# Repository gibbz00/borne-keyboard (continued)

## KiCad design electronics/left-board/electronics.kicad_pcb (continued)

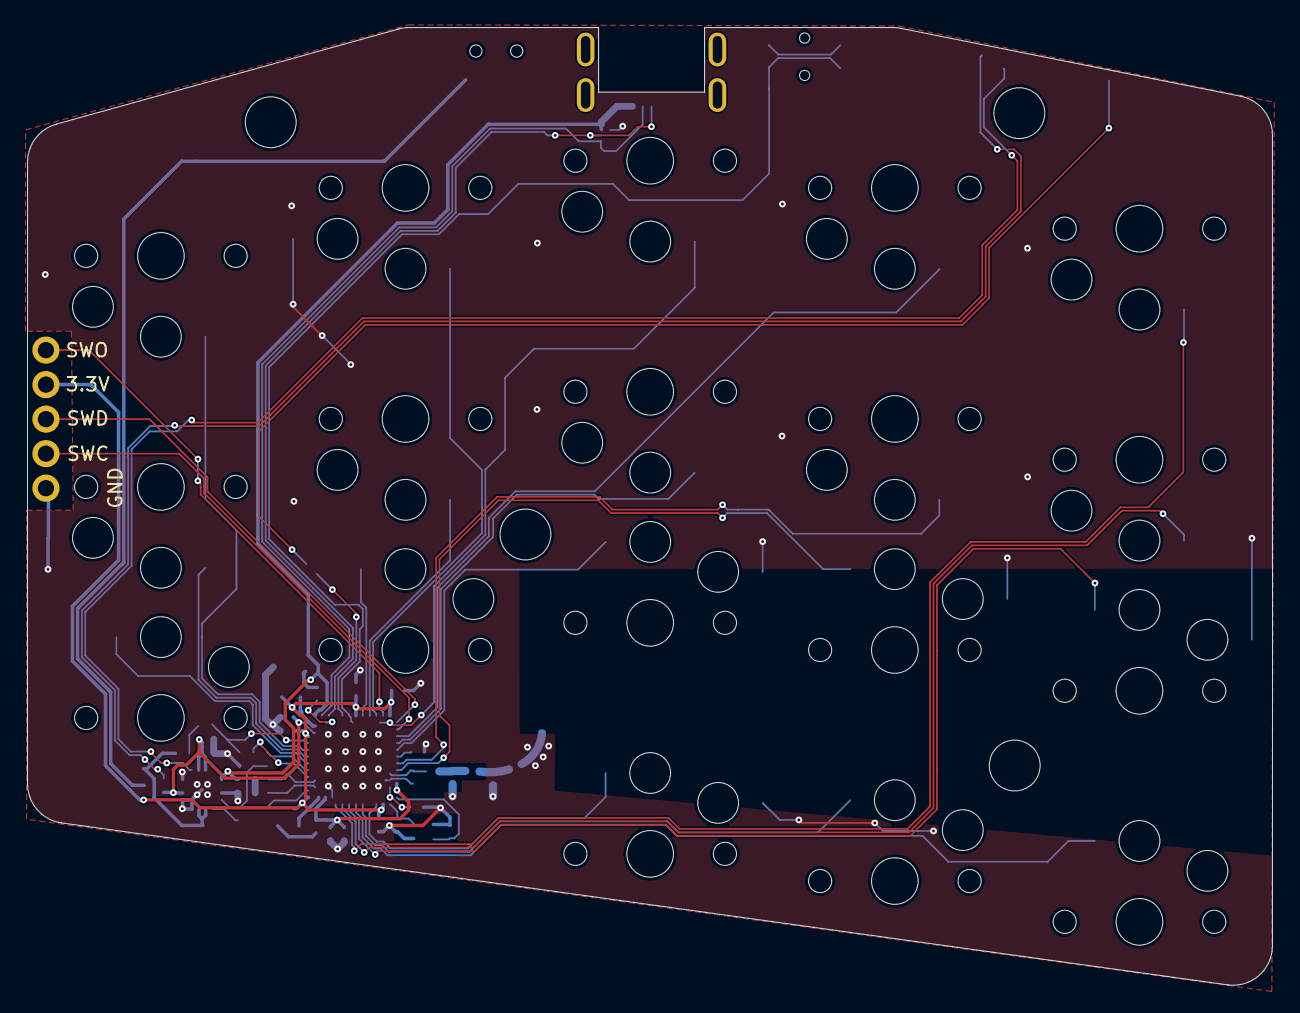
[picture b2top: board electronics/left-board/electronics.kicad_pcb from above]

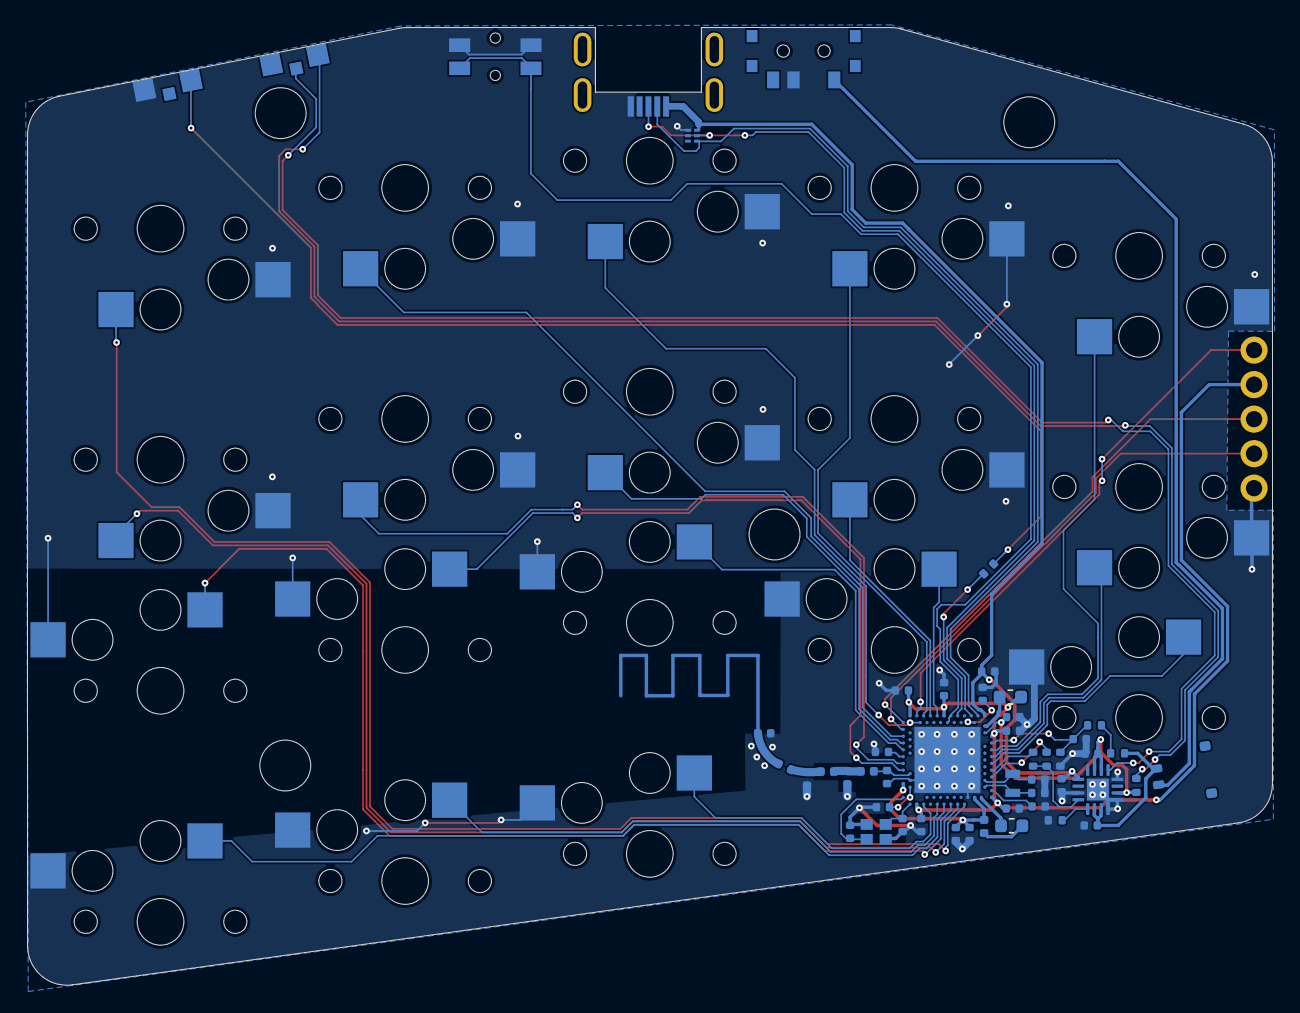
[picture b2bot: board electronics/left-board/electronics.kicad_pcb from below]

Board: 2 copper layers, 91.6 x 70.5 mm, 79 parts (74 on the bottom side), 57 nets.

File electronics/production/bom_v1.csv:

Qty,Reference(s),Value,Footprint,JLC Part,LCSC Part,Manufacturer Part
6,"C1, C3, C12, C16, C23, C24",4.7uF,lib:C_0402_1005Metric,C23733,C368809,CL05A475KP5NRNC
4,"C2, C10, C13, C15",100nF,lib:C_0402_1005Metric,C1525,C1525,CL05B104KA5NNNC
3,"C4, C17, C22",1uF,lib:C_0402_1005Metric,C52923,C52923,CL05A105KO5NNNC
1,C5,100pF,lib:C_0402_1005Metric,C1546,C26409,CL05C101JB5NNNC
1,C6,1.5pF,lib:C_0402_1005Metric,C1552,C170150,CL05C1R5CB5NNNC
1,C7,1nF,lib:C_0402_1005Metric,C1525,C1525,CL05B104KA5NNNC
4,"C8, C9, C19, C20",15pF,lib:C_0402_1005Metric,C1548,C307341,CL05C150JB51PNC
1,C11,1.2pF,lib:C_0402_1005Metric,C1550,C371977,CL05C010CB5NNNC
1,C14,1.0pF,lib:C_0402_1005Metric,C1550,C371977,CL05C010CB5NNNC
1,C18,47nF,lib:C_0402_1005Metric,C26403,C307434,CL05B473KO5NNNC
1,C21,10nF,lib:C_0402_1005Metric,C15195,C15195,CL05B103KB5NNNC
1,C25,N.C,lib:C_0402_1005Metric,C1550,C371977,CL05C010CB5NNNC
2,"D1, D2",LED_Dual_KKA,lib:LED-ARRAY-SMD_3P-L3.0-W2.0-L-FD,,C605447,12-22/BHR6C-A01/2C
1,J1,USB_B_Micro,lib:MICRO-USB-SMD_U-C-M5DD-W-1,,C145798,U-C-M5DD-W-1
1,J2,Battery Connector,lib:Molex_Pico-EZmate_78171-0002_1x02-1MP_P1.20mm_Vertical,C505023,C505023,Molex_Pico-EZmate_78171-0002
1,L1,4.7nH,Inductor_SMD:L_0402_1005Metric,C14033,C76775,MLG1005S3N9BT000
1,L2,15nH,Inductor_SMD:L_0402_1005Metric,C27143,C76763,MLG1005S15NJT000
2,"L3, L4",10uH,Inductor_SMD:L_0402_1005Metric,C1035,C76732,MLF1608E100KTD00
1,L5,2.2nH,Inductor_SMD:L_0402_1005Metric,C14033,C76775,MLG1005S3N9BT000
1,R1,0R,lib:R_0402_1005Metric,C17168,C106231,RC0402FR-070RL
3,"R2, R10, R11",10k,lib:R_0402_1005Metric,C25744,C60490,RC0402FR-0710KL
1,R3,3.9k,lib:R_0402_1005Metric,C51721,C131467,RC0402FR-073K9L
1,R4,1.5k,lib:R_0402_1005Metric,C114759,C114759,RC0402FR-071K5L
1,R5,10M,lib:R_0402_1005Metric,C26082,C138067,RC0402FR-0710ML
2,"R6, R7",2M,lib:R_0402_1005Metric,C138014,C138014,RC0402FR-072ML
1,SW1,SW_Reset,lib:Panasonic_EVQPUL_EVQPUC,C79174,C79174,EVQPUC02K
1,SW2,SW_ON/OFF,lib:SK3296S01L3,C319019,C319019,SK-3296S-01-L3
1,U1,Hot-swap_socket_-_PG151101S11,lib:Kailh_socket_PG1350,C2803348,C2803348,CPG151101S11
1,U2,Hot-swap_socket_-_PG151101S11,lib:Kailh_socket_PG1350,C2803348,C2803348,CPG151101S11
1,U3,Hot-swap_socket_-_PG151101S11,lib:Kailh_socket_PG1350,C2803348,C2803348,CPG151101S11
1,U4,Hot-swap_socket_-_PG151101S11,lib:Kailh_socket_PG1350,C2803348,C2803348,CPG151101S11
1,U5,Hot-swap_socket_-_PG151101S11,lib:Kailh_socket_PG1350,C2803348,C2803348,CPG151101S11
1,U6,Hot-swap_socket_-_PG151101S11,lib:Kailh_socket_PG1350,C2803348,C2803348,CPG151101S11
1,U7,Hot-swap_socket_-_PG151101S11,lib:Kailh_socket_PG1350,C2803348,C2803348,CPG151101S11
1,U8,Hot-swap_socket_-_PG151101S11,lib:Kailh_socket_PG1350,C2803348,C2803348,CPG151101S11
1,U9,Hot-swap_socket_-_PG151101S11,lib:Kailh_socket_PG1350,C2803348,C2803348,CPG151101S11
1,U10,Hot-swap_socket_-_PG151101S11,lib:Kailh_socket_PG1350,C2803348,C2803348,CPG151101S11
1,U11,nRF52840,Package_DFN_QFN:Nordic_AQFN-73-1EP_7x7mm_P0.5mm,C1851953,C1851953,NRF52840-QIAA-R
1,U12,Hot-swap_socket_-_PG151101S11,lib:Kailh_socket_PG1350,C2803348,C2803348,CPG151101S11
1,U13,Hot-swap_socket_-_PG151101S11,lib:Kailh_socket_PG1350,C2803348,C2803348,CPG151101S11
1,U14,Hot-swap_socket_-_PG151101S11,lib:Kailh_socket_PG1350,C2803348,C2803348,CPG151101S11
1,U15,Hot-swap_socket_-_PG151101S11,lib:Kailh_socket_PG1350,C2803348,C2803348,CPG151101S11
1,U16,Hot-swap_socket_-_PG151101S11,lib:Kailh_socket_PG1350,C2803348,C2803348,CPG151101S11
1,U17,Hot-swap_socket_-_PG151101S11,lib:Kailh_socket_PG1350,C2803348,C2803348,CPG151101S11
1,U18,Hot-swap_socket_-_PG151101S11,lib:Kailh_socket_PG1350,C2803348,C2803348,CPG151101S11
1,U19,Hot-swap_socket_-_PG151101S11,lib:Kailh_socket_PG1350,C2803348,C2803348,CPG151101S11
1,U20,ESDR0502NMUTAG,lib:ESDR0502NMUTAG,C327480,C327480,ESDR0502NMUTBG
1,U21,BQ24075RGT,lib:VQFN-16-1EP_3x3mm_P0.5mm_EP1.6x1.6mm,C15464,C15464,BQ24075RGTR
1,Y1,32MHz,lib:Crystal_SMD_2016-4Pin_2.0x1.6mm,C255896,C255896,Q22FA1280001800
1,Y2,32.768 kHz,lib:Crystal_SMD_2012-2Pin_2.0x1.2mm,C93231,C97607,SC20S-12.5PF20PPM

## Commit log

2022-11-06 v1 launch
2022-11-06 bootloader and zmk submodules
2022-11-06 submodule updates
2022-11-06 zmk submodule update: layout
2022-11-07 added README
2022-11-07 add showcase images
2022-11-07 add showcase image to README
2022-11-10 updating wording in readme
2022-11-10 README title change
2022-11-23 license holder clarification
2022-11-23 readme showcase image update
2022-11-23 reflect github actions method in readme
2022-11-23 zmk resources url cleanup
2022-11-23 minor readme changes
2022-12-11 add keyboard layout link in readme
2022-12-11 readme spelling
2023-02-09 minor readme changes.
2023-02-09 readme title formatting
2023-02-12 interest check announcement
2023-07-18 Publish v2
2023-07-18 Update README.md image links.
2023-07-19 Extend ground plane fill.
2023-07-19 Mouse bite clearance accomodation.
2023-07-21 Remove old bom file.
2023-07-21 Component metadata updates:
    * Use official footprints for 0402 caps and resistors.
    * Use correct JLC and LCSC part numbers for the choc switches.
2023-07-21 Value update for battery connector and reset switch.
2023-07-21 BOM value updates:
    USB C Receptable
    Molex connector.
2023-07-21 Add JLC Part number to LEDs
2023-07-21 Use official symbol for charging IC.
2023-07-21 Electronics lib: remove .bak files.
2023-07-21 Remove unused Micro USB design files.
2023-07-21 Remove unused battery switch design files.
2023-07-22 electronics/right: Fix schema and PCB references parity.
2023-07-22 electronics/left: Fix schema and PCB references parity.
2023-07-22 Remove footprint placement silkscreen lines.
2023-07-23 electronics/right: Add missing battery pads.
2023-07-23 Make sure left and right halves produce the same BOM.
2023-07-23 Enclosure: New screw dimensions.
2023-07-24 Rename stp files such that 3x5 and 3x6 can be differentiated by name.
2023-08-12 Fix incorrect manufacturer part numbers.
